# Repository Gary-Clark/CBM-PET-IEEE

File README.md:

# CBM-PET-IEEE
File system for the CBM pet

This project implements an IEEE interface between a CBM PET and an Arduino MEGA2560
and works as a simple disk emulator allowing BASIC SAVE and LOAD commands to read/write programs to an SD card.

As the arduino ports are tri-state, the interface requires no buffer components and just connects the IEEE-488 spec connector directly to the Arduino pins and the SD card via the SPI port. This arrangement has been tested with a genuine 8050 sharing the same bus and works correctly.

Currently only supports the LOAD"filename",9 command, the SAVE"filename",9 command and the LOAD"$",9 commands, however each also can interpret drive numbers (ie LOAD"1:filename",9 or LOAD"$4",9). Files are stores in standard FAT 8.3 format as PET .PRG files (easily found online and downloaded) but the filename must be 8 characters or less (ie TANKS.PRG) and stored in a folder with names 0 to 9 to simulate 10 drives.

It is intended to expand the operation to cover sequential files and an command/error channel.

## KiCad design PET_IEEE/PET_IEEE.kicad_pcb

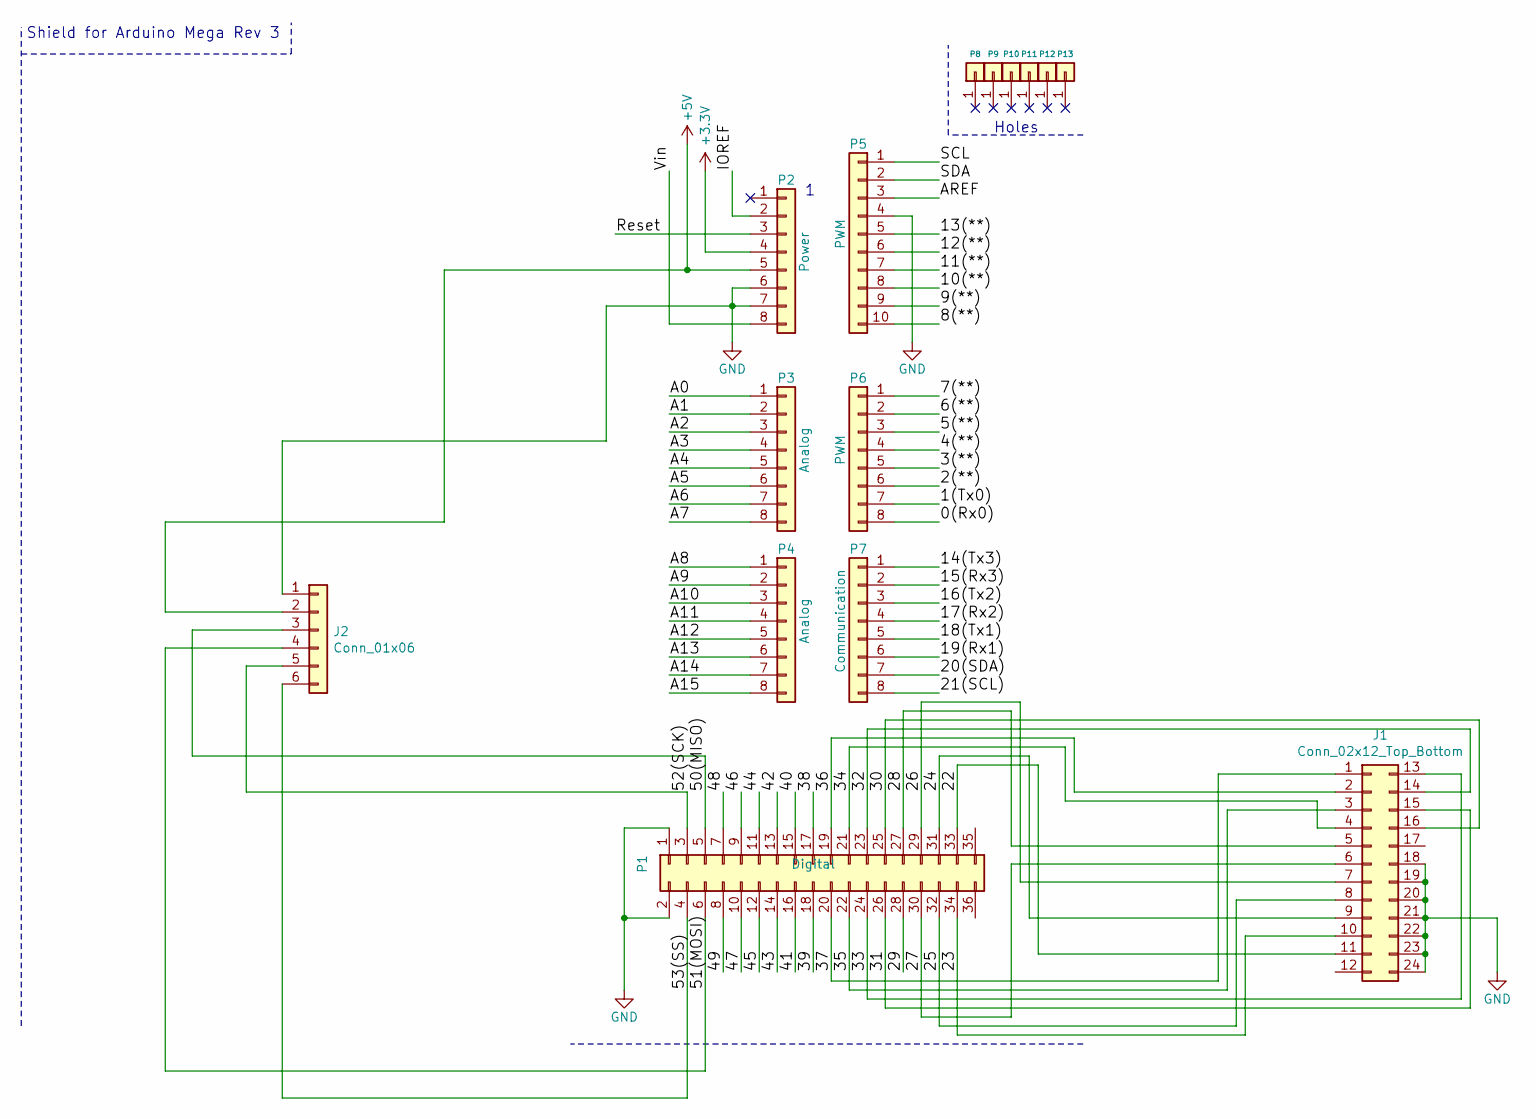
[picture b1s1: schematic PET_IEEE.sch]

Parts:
J1: Conn_02x12_Top_Bottom; GPIB
J2: Conn_01x06; PinHeader_1x06_P2.54mm_Vertical
P1: Digital; Socket_Strip_Arduino_2x18
P2: Power; Socket_Strip_Arduino_1x08
P3, P4: Analog; Socket_Strip_Arduino_1x08
P5: PWM; Socket_Strip_Arduino_1x10
P6: PWM; Socket_Strip_Arduino_1x08
P7: Communication; Socket_Strip_Arduino_1x08
P8, P9, P10, P11, P12, P13: CONN_01X01; Arduino_1pin

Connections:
+3V3: P2.4
+5V: J2.2, P2.5
/0(Rx0): P6.8
/1(Tx0): P6.7
/2(**): P6.6
/3(**): P6.5
/4(**): P6.4
/5(**): P6.3
/6(**): P6.2
/7(**): P6.1
/8(**): P5.10
/9(**): P5.9
/10(**): P5.8
/11(**): P5.7
/12(**): P5.6
/13(**): P5.5
/14(Tx3): P7.1
/15(Rx3): P7.2
/16(Tx2): P7.3
/17(Rx2): P7.4
/18(Tx1): P7.5
/19(Rx1): P7.6
/20(SDA): P7.7
/21(SCL): P7.8
/22: J1.11, P1.33
/23: J1.10, P1.34
/24: J1.9, P1.31
/25: J1.8, P1.32
/26: J1.7, P1.29
/27: J1.6, P1.30
/28: J1.5, P1.27
/29: P1.28
/30: J1.16, P1.25
/31: J1.15, P1.26
/32: J1.14, P1.23
/33: J1.13, P1.24
/34: J1.4, P1.21
/35: J1.3, P1.22
/36: J1.2, P1.19
/37: J1.1, P1.20
/38: P1.17
/39: P1.18
/40: P1.15
/41: P1.16
/42: P1.13
/43: P1.14
/44: P1.11
/45: P1.12
/46: P1.9
/47: P1.10
/48: P1.7
/49: P1.8
/50(MISO): J2.3, P1.5
/51(MOSI): J2.4, P1.6
/52(SCK): J2.5, P1.3
/53(SS): J2.6, P1.4
/A0: P3.1
/A1: P3.2
/A2: P3.3
/A3: P3.4
/A4: P3.5
/A5: P3.6
/A6: P3.7
/A7: P3.8
/A8: P4.1
/A9: P4.2
/A10: P4.3
/A11: P4.4
/A12: P4.5
/A13: P4.6
/A14: P4.7
/A15: P4.8
/AREF: P5.3
/IOREF: P2.2
/Reset: P2.3
/SCL: P5.1
/SDA: P5.2
/Vin: P2.8
GND: J1.18, J1.19, J1.20, J1.21, J1.22, J1.23, J1.24, J2.1, P1.1, P1.2, P2.6, P2.7, P5.4

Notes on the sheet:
Shield for Arduino Mega Rev 3
Holes

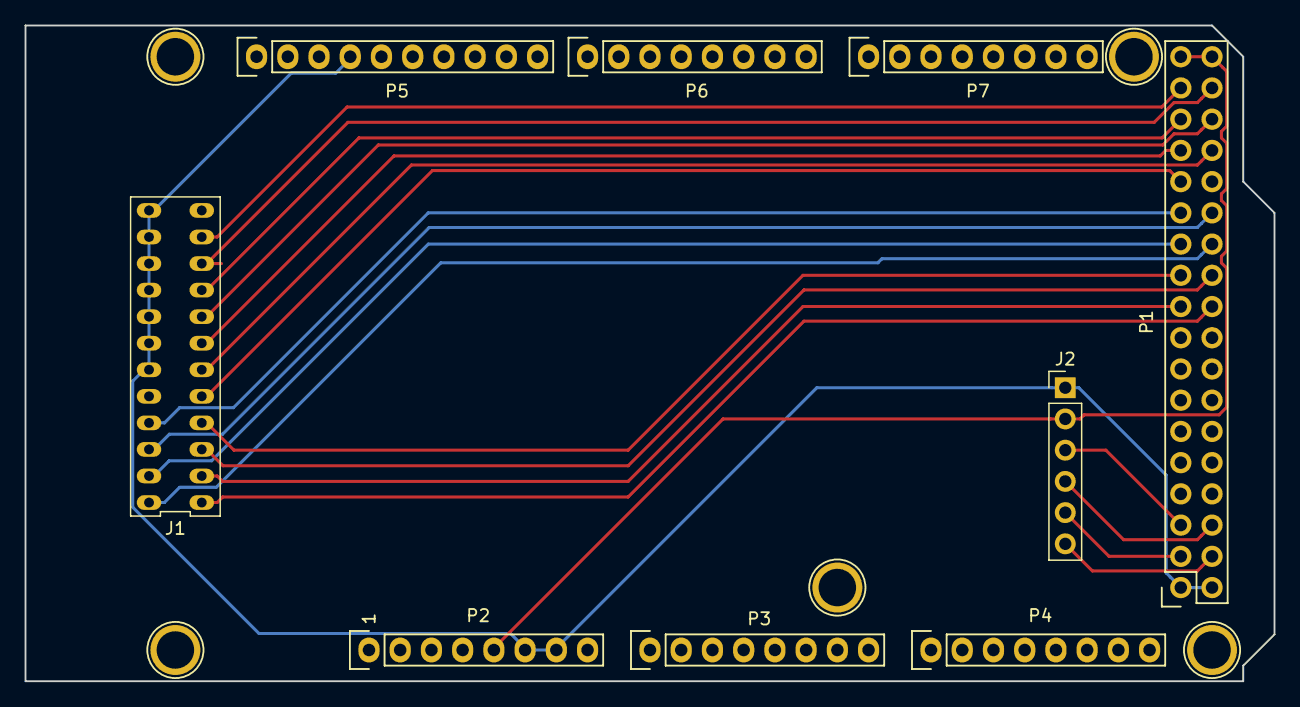
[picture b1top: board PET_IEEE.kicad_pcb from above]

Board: 2 copper layers, 101.6 x 53.3 mm, 14 parts (0 on the bottom side), 21 nets.

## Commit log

2019-10-12 Create PCB
2019-10-12 Create Parts
2019-10-26 Add files via upload
    A largely working version.
    All file names need to be 8.3 format ending in .PRG
    any spaces must be filled with 0
    eg TANKS000.PRG (next job will be to have variable length file names)
2019-10-26 Add files via upload
    This V8 works
2019-11-25 Update Parts
2019-11-25 Create PRG files
2023-03-30 Create IEEE_488_V14
